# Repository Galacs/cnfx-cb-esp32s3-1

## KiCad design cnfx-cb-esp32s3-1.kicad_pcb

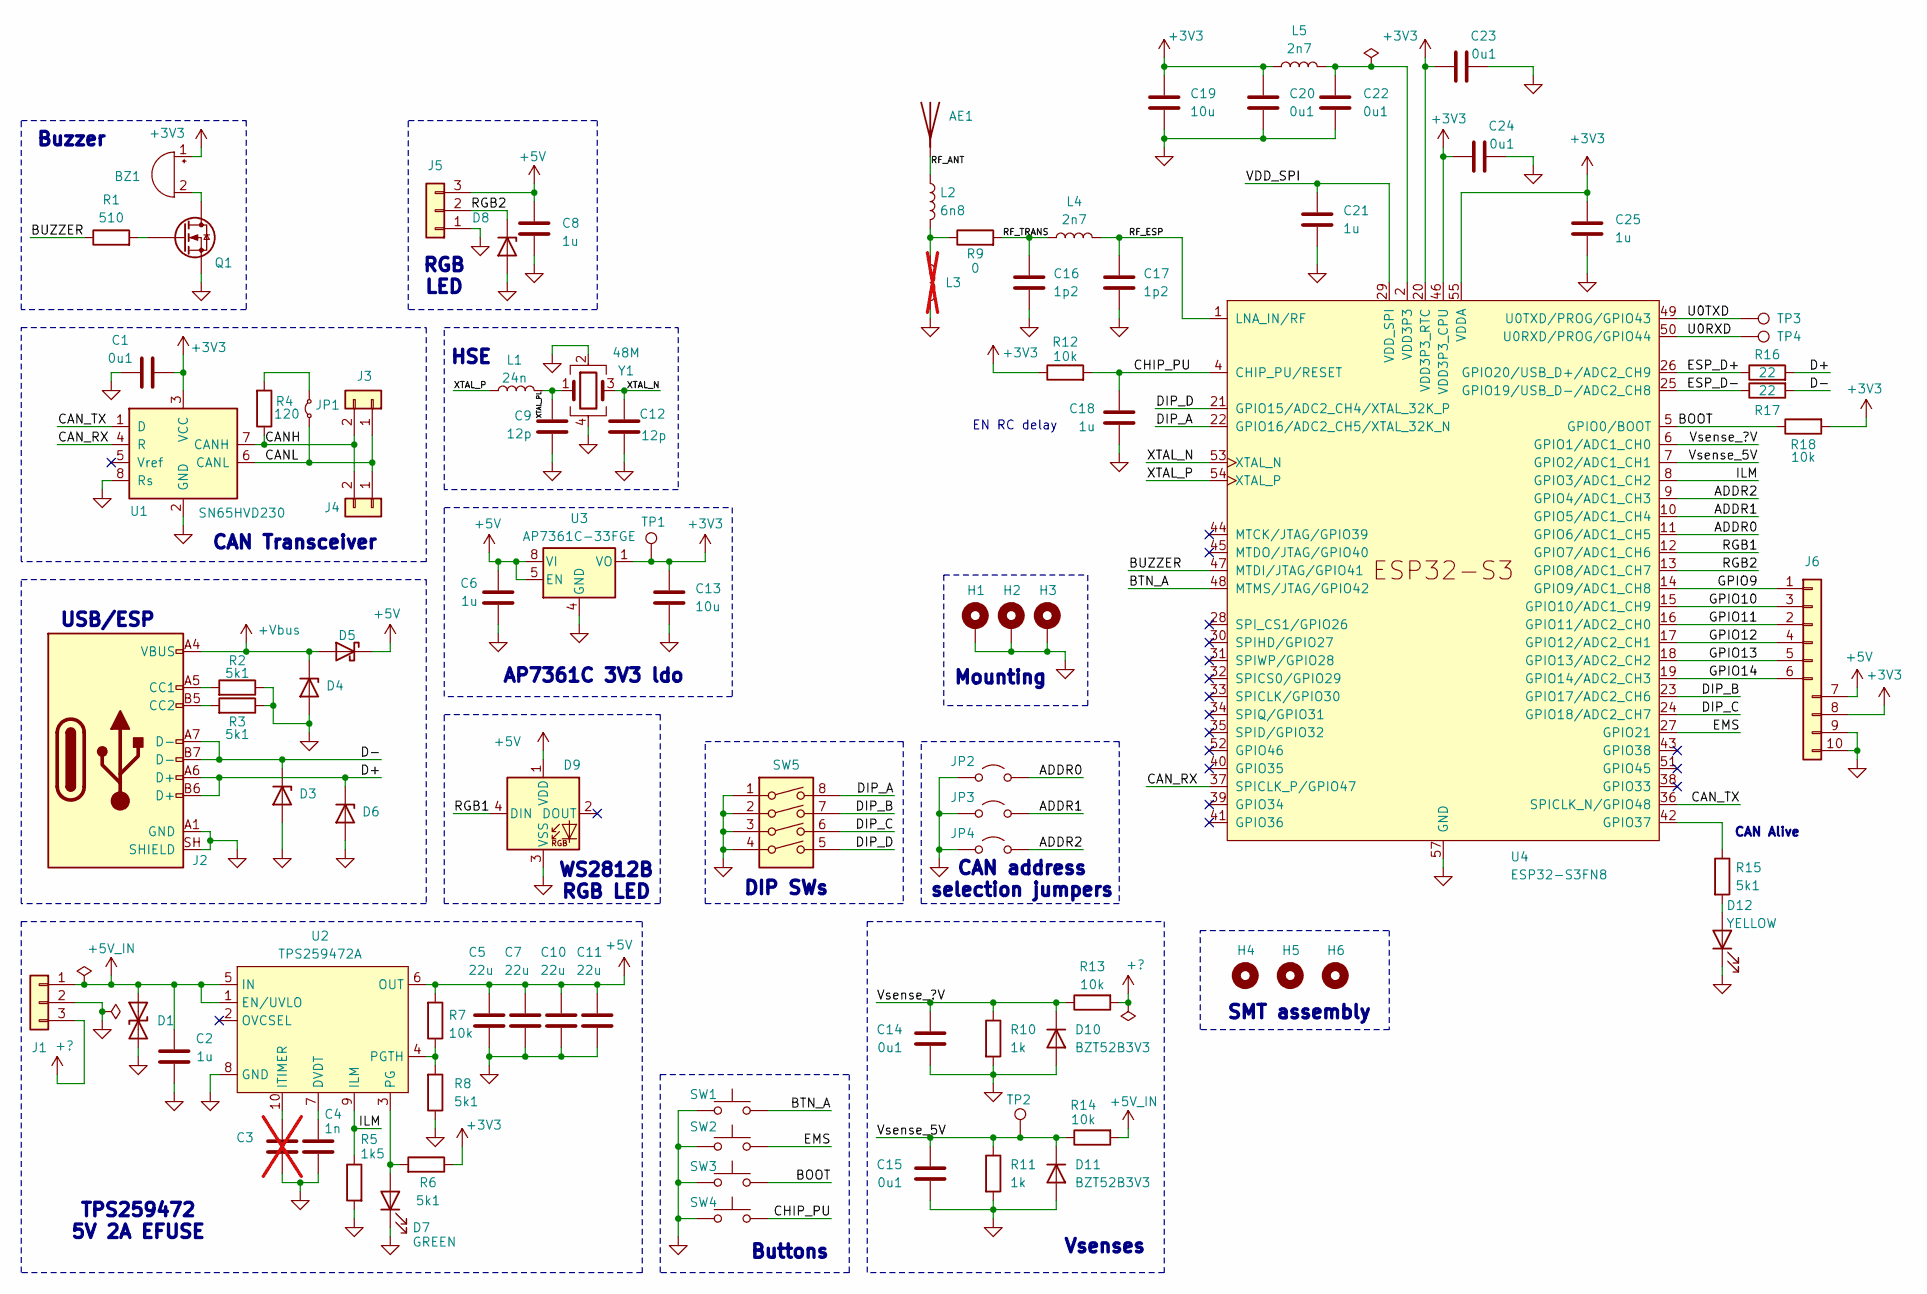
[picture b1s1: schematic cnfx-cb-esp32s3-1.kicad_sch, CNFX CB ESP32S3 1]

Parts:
AE1: Antenna; Johanson_2450AT18x100; Manufacturer Part Number RFANT3216120A5T; JLCPCB Part # C127629
BZ1: Buzzer; MagneticBuzzer_Huaneng_MLT-5020; Manufacturer Part Number MLT-5020; JLCPCB Part # C94598
C1, C14, C15, C20, C22, C23, C24: 0u1; C_0402_1005Metric; Manufacturer Part Number CL05B104KB54PNC; JLCPCB Part # C307331
C2, C6, C8, C18, C21, C25: 1u; C_0402_1005Metric; Manufacturer Part Number CL05A105KA5NQNC; JLCPCB Part # C52923
C3: C; C_0402_1005Metric; not fitted
C4: 1n; C_0402_1005Metric; Manufacturer Part Number 0402B102K500NT; JLCPCB Part # C1523
C5, C7, C10, C11: 22u; C_0805_2012Metric; Manufacturer Part Number CL21A226MAQNNNE; JLCPCB Part # C45783
C9, C12: 12p; C_0402_1005Metric; Manufacturer Part Number 0402CG120J500NT; JLCPCB Part # C1547
C13, C19: 10u; C_0402_1005Metric; Manufacturer Part Number CL05A106MQ5NUNC; JLCPCB Part # C15525
C16, C17: 1p2; C_0402_1005Metric; Manufacturer Part Number GJM1555C1H1R2WB01D; JLCPCB Part # C76899
D1: SMAJ6.0CA; D_SMA; Manufacturer Part Number SMAJ6.0CA; JLCPCB Part # C19077526
D3, D4, D6, D8: H5VU10U; Diode_DFN1006; Manufacturer Part Number H5VU10U; JLCPCB Part # C22395519
D5: D_Schottky; D_SMA; Manufacturer Part Number SS54; JLCPCB Part # C22452
D7: GREEN; LED_0805_2012Metric; Manufacturer Part Number KT-0805G; JLCPCB Part # C2297
D9: WS2812B; LED_WS2812B_PLCC4_5.0x5.0mm_P3.2mm; Manufacturer Part Number WS2812B-V5/W; JLCPCB Part # C2874885
D10, D11: BZT52B3V3; D_SOD-123; Manufacturer Part Number BZT52B3V3; JLCPCB Part # C19077392
D12: YELLOW; LED_0805_2012Metric; Manufacturer Part Number KT-0805Y; JLCPCB Part # C2296
H1, H2, H3: MountingHole_Pad; MountingHole_3.2mm_M3_Pad_Via
H4, H5, H6: MountingHole; ToolingHole_1.152mm
J1: Conn_01x03; JST_XH_B3B-XH-A_1x03_P2.50mm_Vertical; Manufacturer Part Number B3B-XH-A(LF)(SN); JLCPCB Part # C144394
J2: USB_C_Receptacle_USB2.0_14P; USB_C_Receptacle_HRO_TYPE-C-31-M-12; Manufacturer Part Number TYPE-C16PIN; JLCPCB Part # C393939
J3, J4: Conn_01x02; JST_XH_B2B-XH-A_1x02_P2.50mm_Vertical; Manufacturer Part Number B2B-XH-A(LF)(SN); JLCPCB Part # C158012
J5: Conn_01x03; JST_PH_S3B-PH-K_1x03_P2.00mm_Horizontal; Manufacturer Part Number S3B-PH-K-S(LF)(SN); JLCPCB Part # C157929
J6: Conn_01x10; PinHeader_2x05_P2.54mm_Vertical
JP1: Jumper_2_Small_Bridged; PinHeader_1x02_P2.54mm_Vertical
JP2, JP3, JP4: Jumper_2_Open; SolderJumper-2_P1.3mm_Open_RoundedPad1.0x1.5mm
L1: 24n; L_0402_1005Metric; Manufacturer Part Number LQW15AN24NG00D; JLCPCB Part # C167472
L2: 6n8; L_0402_1005Metric; Manufacturer Part Number LQG15HS6N8J02D; JLCPCB Part # C77110
L3: L; L_0402_1005Metric; not fitted
L4, L5: 2n7; L_0402_1005Metric; Manufacturer Part Number LQG15HS2N7S02D; JLCPCB Part # C77108
Q1: Q_NMOS; SOT-323_SC-70; Manufacturer Part Number BSS138W; JLCPCB Part # C28646265
R1: 510; R_0402_1005Metric; Manufacturer Part Number 0402WGF5100TCE; JLCPCB Part # C25123
R2, R3, R6, R8, R15: 5k1; R_0402_1005Metric; Manufacturer Part Number 0402WGF5101TCE; JLCPCB Part # C25905
R4: 120; R_1206_3216Metric; Manufacturer Part Number 1206W4F1200T5E; JLCPCB Part # C17909
R5: 1k5; R_0402_1005Metric; Manufacturer Part Number 0402WGF1501TCE; JLCPCB Part # C25867
R7, R12, R13, R14, R18: 10k; R_0402_1005Metric; Manufacturer Part Number 0402WGF1002TCE; JLCPCB Part # C25744
R9: 0; R_0402_1005Metric; Manufacturer Part Number 0402WGF0000TCE; JLCPCB Part # C17168
R10, R11: 1k; R_0402_1005Metric; Manufacturer Part Number 0402WGF1001TCE; JLCPCB Part # C11702
R16, R17: 22; R_0402_1005Metric; Manufacturer Part Number 0402WGF220JTCE; JLCPCB Part # C25092
SW1, SW3, SW4: SW_Push; SW_SPST_TS-1088-xR020; Manufacturer Part Number TS-1088-AR02016; JLCPCB Part # C720477
SW2: SW_Push; JST_XH_B2B-XH-A_1x02_P2.50mm_Vertical; Manufacturer Part Number B2B-XH-A(LF)(SN); JLCPCB Part # C158012
SW5: SW_DIP_x04; SW_DIP_SPSTx04_Slide_KingTek_DSHP04TS_W7.62mm_P1.27mm; Manufacturer Part Number DSHP04TSGER; JLCPCB Part # C3293144
TP1, TP2: TestPoint; TestPoint_Pad_D2.0mm
TP3, TP4: TestPoint; TestPoint_Pad_D1.0mm
U1: SN65HVD230; SOIC-8_3.9x4.9mm_P1.27mm; Manufacturer Part Number SN65HVD230DR; JLCPCB Part # C12084
U2: TPS259472A; Texas_RPW0010A_VQFN-HR-10_2x2mm_P0.5mm; Manufacturer Part Number TPS259472ARPWR; JLCPCB Part # C3662789
U3: AP7361C-33FGE; DFN-8-1EP_3x3mm_P0.65mm_EP1.6x2.56mm_ThermalVias; Manufacturer Part Number AP7361C-33FGE-7; JLCPCB Part # C151007
U4: ESP32-S3FN8; QFN-56-1EP_7x7mm_P0.4mm_EP4x4mm_ThermalVias; Manufacturer Part Number ESP32-S3FH4R2; JLCPCB Part # C3013940
Y1: 48M; Crystal_SMD_2016-4Pin_2.0x1.6mm; Manufacturer Part Number R940000096; JLCPCB Part # C7206306

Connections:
+3V3: BZ1.1 (+), C1.1, C13.1, C19.1, C20.1, C23.1, C24.1, C25.1, J6.8, L5.1, R6.1, R12.1, R18.2, TP1.1 (1_1), U1.3 (VCC), U3.1 (VO), U4.20 (VDD3P3_RTC), U4.46 (VDD3P3_CPU), U4.55 (VDDA), U4.56 (VDDA)
+5V: C5.1, C6.1, C7.1, C8.1, C10.1, C11.1, D5.1 (K), D9.1 (VDD), J5.3, J6.7, R7.2, U2.6 (OUT), U3.5 (EN), U3.8 (VI)
+5V_IN: C2.2, D1.1 (A1), J1.1, R14.2, U2.1 (EN/UVLO), U2.5 (IN)
+?: J1.3, R13.2
+Vbus: D4.1 (K), D5.2 (A), J2.A4 (VBUS), J2.A9 (VBUS), J2.B4 (VBUS), J2.B9 (VBUS)
/ADDR0: JP2.2 (B), U4.11 (GPIO6/ADC1_CH5)
/ADDR1: JP3.2 (B), U4.10 (GPIO5/ADC1_CH4)
/ADDR2: JP4.2 (B), U4.9 (GPIO4/ADC1_CH3)
/BOOT: R18.1, SW3.2, U4.5 (GPIO0/BOOT)
/BTN_A: SW1.2, U4.48 (MTMS/JTAG/GPIO42)
/BUZZER: R1.1, U4.47 (MTDI/JTAG/GPIO41)
/CANH: J3.2, J4.2, R4.1, U1.7 (CANH)
/CANL: J3.1, J4.1, JP1.1 (A), U1.6 (CANL)
/CAN_RX: U1.4 (R), U4.37 (SPICLK_P/GPIO47)
/CAN_TX: U1.1 (D), U4.36 (SPICLK_N/GPIO48)
/CHIP_PU: C18.1, R12.2, SW4.2, U4.4 (CHIP_PU/RESET)
/D+: D6.1 (K), J2.A6 (D+), J2.B6 (D+), R16.2
/D-: D3.1 (K), J2.A7 (D-), J2.B7 (D-), R17.2
/DIP_A: SW5.8, U4.22 (GPIO16/ADC2_CH5/XTAL_32K_N)
/DIP_B: SW5.7, U4.23 (GPIO17/ADC2_CH6)
/DIP_C: SW5.6, U4.24 (GPIO18/ADC2_CH7)
/DIP_D: SW5.5, U4.21 (GPIO15/ADC2_CH4/XTAL_32K_P)
/EMS: SW2.2, U4.27 (GPIO21)
/ESP_D+: R16.1, U4.26 (GPIO20/USB_D+/ADC2_CH9)
/ESP_D-: R17.1, U4.25 (GPIO19/USB_D-/ADC2_CH8)
/GPIO9: J6.1, U4.14 (GPIO9/ADC1_CH8)
/GPIO10: J6.3, U4.15 (GPIO10/ADC1_CH9)
/GPIO11: J6.2, U4.16 (GPIO11/ADC2_CH0)
/GPIO12: J6.4, U4.17 (GPIO12/ADC2_CH1)
/GPIO13: J6.5, U4.18 (GPIO13/ADC2_CH2)
/GPIO14: J6.6, U4.19 (GPIO14/ADC2_CH3)
/ILM: R5.1, U2.9 (ILM), U4.8 (GPIO3/ADC1_CH2)
/RF_ANT: AE1.1 (A_1), L2.1
/RF_ESP: C17.1, L4.2, U4.1 (LNA_IN/RF)
/RF_TRANS: C16.1, L4.1, R9.2
/RGB1: D9.4 (DIN), U4.12 (GPIO7/ADC1_CH6)
/RGB2: D8.1 (K), J5.2, U4.13 (GPIO8/ADC1_CH7)
/U0RXD: TP4.1 (1_1), U4.50 (U0RXD/PROG/GPIO44)
/U0TXD: TP3.1 (1_1), U4.49 (U0TXD/PROG/GPIO43)
/VDD_SPI: C21.1, U4.29 (VDD_SPI)
/Vsense_5V: C15.1, D11.1 (K), R11.1, R14.1, TP2.1 (1_1), U4.7 (GPIO2/ADC1_CH1)
/Vsense_?V: C14.1, D10.1 (K), R10.1, R13.1, U4.6 (GPIO1/ADC1_CH0)
/XTAL_N: C12.1, U4.53 (XTAL_N), Y1.3
/XTAL_P: L1.1, U4.54 (XTAL_P)
/XTAL_PL: C9.2, L1.2, Y1.1
GND: C1.2, C2.1, C3.2, C4.2, C5.2, C6.2, C7.2, C8.2, C9.1, C10.2, C11.2, C12.2, C13.2, C14.2, C15.2, C16.2, C17.2, C18.2, C19.2, C20.2, C21.2, C22.2, C23.2, C24.2, C25.2, D1.2 (A2), D3.2 (A), D4.2 (A), D6.2 (A), D7.1 (K), D8.2 (A), D9.3 (VSS), D10.2 (A), D11.2 (A), D12.1 (K), H1.1 (1_1), H2.1 (1_1), H3.1 (1_1), J1.2, J2.A1 (GND), J2.A12 (GND), J2.B1 (GND), J2.B12 (GND), J2.SH (SHIELD), J5.1, J6.9, J6.10, JP2.1 (A), JP3.1 (A), JP4.1 (A), L3.2, Q1.2 (S), R2.1, R3.1, R5.2, R8.1, R10.2, R11.2, SW1.1, SW2.1, SW3.1, SW4.1, SW5.1, SW5.2, SW5.3, SW5.4, U1.2 (GND), U1.8 (Rs), U2.8 (GND), U3.4 (GND), U3.9 (GND), U4.57 (GND), Y1.2, Y1.4
unnamed: BZ1.2 (-), Q1.3 (D)
unnamed: D7.2 (A), R6.2, U2.3 (PG)
unnamed: D12.2 (A), R15.2
unnamed: J2.A5 (CC1), R2.2
unnamed: J2.B5 (CC2), R3.2
unnamed: JP1.2 (B), R4.2
unnamed: L2.2, L3.1, R9.1
unnamed: Q1.1 (G), R1.2
unnamed: C4.1, U2.7 (DVDT)
unnamed: C3.1, U2.10 (ITIMER)
unnamed: R7.1, R8.2, U2.4 (PGTH)
unnamed: R15.1, U4.42 (GPIO37)
VDD3P3: C22.1, L5.2, U4.2 (VDD3P3), U4.3 (VDD3P3)

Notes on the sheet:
SMT assembly
CAN Alive
Buzzer
WS2812B RGB LED
Vsenses
CAN Transceiver
CAN address selection jumpers
RGB LED
AP7361C 3V3 ldo
Buttons
TPS259472 5V 2A EFUSE
HSE
Mounting
USB/ESP
EN RC delay
DIP SWs

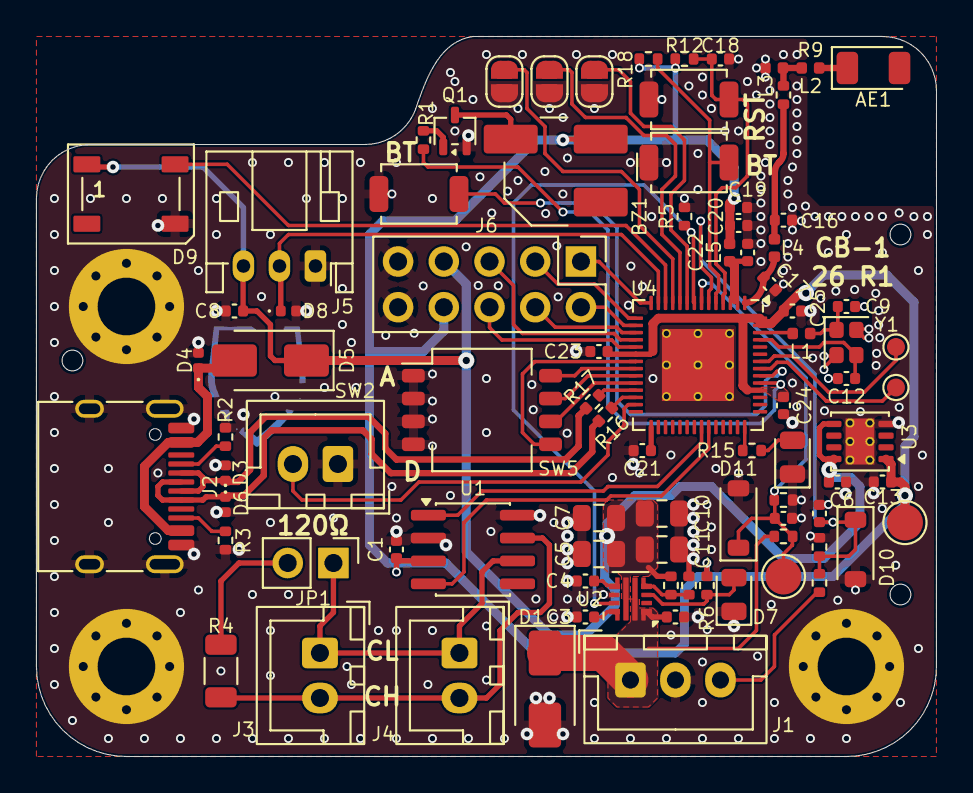
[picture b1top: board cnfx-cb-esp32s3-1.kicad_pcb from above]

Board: 4 copper layers, 50.0 x 40.0 mm, 92 parts (0 on the bottom side), 59 nets.

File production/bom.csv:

Designator,Footprint,Quantity,Value,LCSC Part #
AE1,Johanson_2450AT18x100,1,Antenna,C127629
BZ1,MagneticBuzzer_Huaneng_MLT-5020,1,Buzzer,C94598
"C1, C14, C15, C20, C22, C23, C24",0402,7,0u1,C307331
"C10, C11, C5, C7",0805,4,22u,C45783
"C12, C9",0402,2,12p,C1547
"C13, C19",0402,2,10u,C15525
"C16, C17",0402,2,1p2,C76899
"C18, C2, C21, C25, C6, C8",0402,6,1u,C52923
C4,0402,1,1n,C1523
D1,D_SMA,1,SMAJ6.0CA,C19077526
"D10, D11",D_SOD-123,2,BZT52B3V3,C19077392
D12,0805,1,YELLOW,C2296
"D3, D4, D6, D8",Diode_DFN1006,4,H5VU10U,C22395519
D5,D_SMA,1,D_Schottky,C22452
D7,0805,1,GREEN,C2297
D9,LED_WS2812B_PLCC4_5.0x5.0mm_P3.2mm,1,WS2812B,C2874885
J1,JST_XH_B3B-XH-A_1x03_P2.50mm_Vertical,1,Conn_01x03,C144394
J2,USB_C_Receptacle_HRO_TYPE-C-31-M-12,1,USB_C_Receptacle_USB2.0_14P,C393939
"J3, J4",JST_XH_B2B-XH-A_1x02_P2.50mm_Vertical,2,Conn_01x02,C158012
J5,JST_PH_S3B-PH-K_1x03_P2.00mm_Horizontal,1,Conn_01x03,C157929
L1,0402,1,24n,C167472
L2,0402,1,6n8,C77110
"L4, L5",0402,2,2n7,C77108
Q1,SOT-323_SC-70,1,Q_NMOS,C28646265
R1,0402,1,510,C25123
"R10, R11",0402,2,1k,C11702
"R12, R13, R14, R18, R7",0402,5,10k,C25744
"R15, R2, R3, R6, R8",0402,5,5k1,C25905
"R16, R17",0402,2,22,C25092
R4,1206,1,120,C17909
R5,0402,1,1k5,C25867
R9,0402,1,0,C17168
"SW1, SW3, SW4",SW_SPST_TS-1088-xR020,3,SW_Push,C720477
SW2,JST_XH_B2B-XH-A_1x02_P2.50mm_Vertical,1,SW_Push,C158012
SW5,SW_DIP_SPSTx04_Slide_KingTek_DSHP04TS_W7.62mm_P1.27mm,1,SW_DIP_x04,C3293144
U1,SOIC-8_3.9x4.9mm_P1.27mm,1,SN65HVD230,C12084
U2,Texas_RPW0010A_VQFN-HR-10_2x2mm_P0.5mm,1,TPS259472A,C3662789
U3,DFN-8-1EP_3x3mm_P0.65mm_EP1.6x2.56mm_ThermalVias,1,AP7361C-33FGE,C151007
U4,QFN-56-1EP_7x7mm_P0.4mm_EP4x4mm_ThermalVias,1,ESP32-S3FN8,C3013940
Y1,Crystal_SMD_2016-4Pin_2.0x1.6mm,1,48M,C7206306
